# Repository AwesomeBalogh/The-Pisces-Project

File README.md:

The Pisces Project
By Bennett Balogh 
(Name subject to change Orion?)

This is a PCB with a 68 key layout like the ikki 68 aurora with left f keys using atmega chip.
The ultimate goal is to create a fully wireless pcb with wireless charging from a charger under the desk.

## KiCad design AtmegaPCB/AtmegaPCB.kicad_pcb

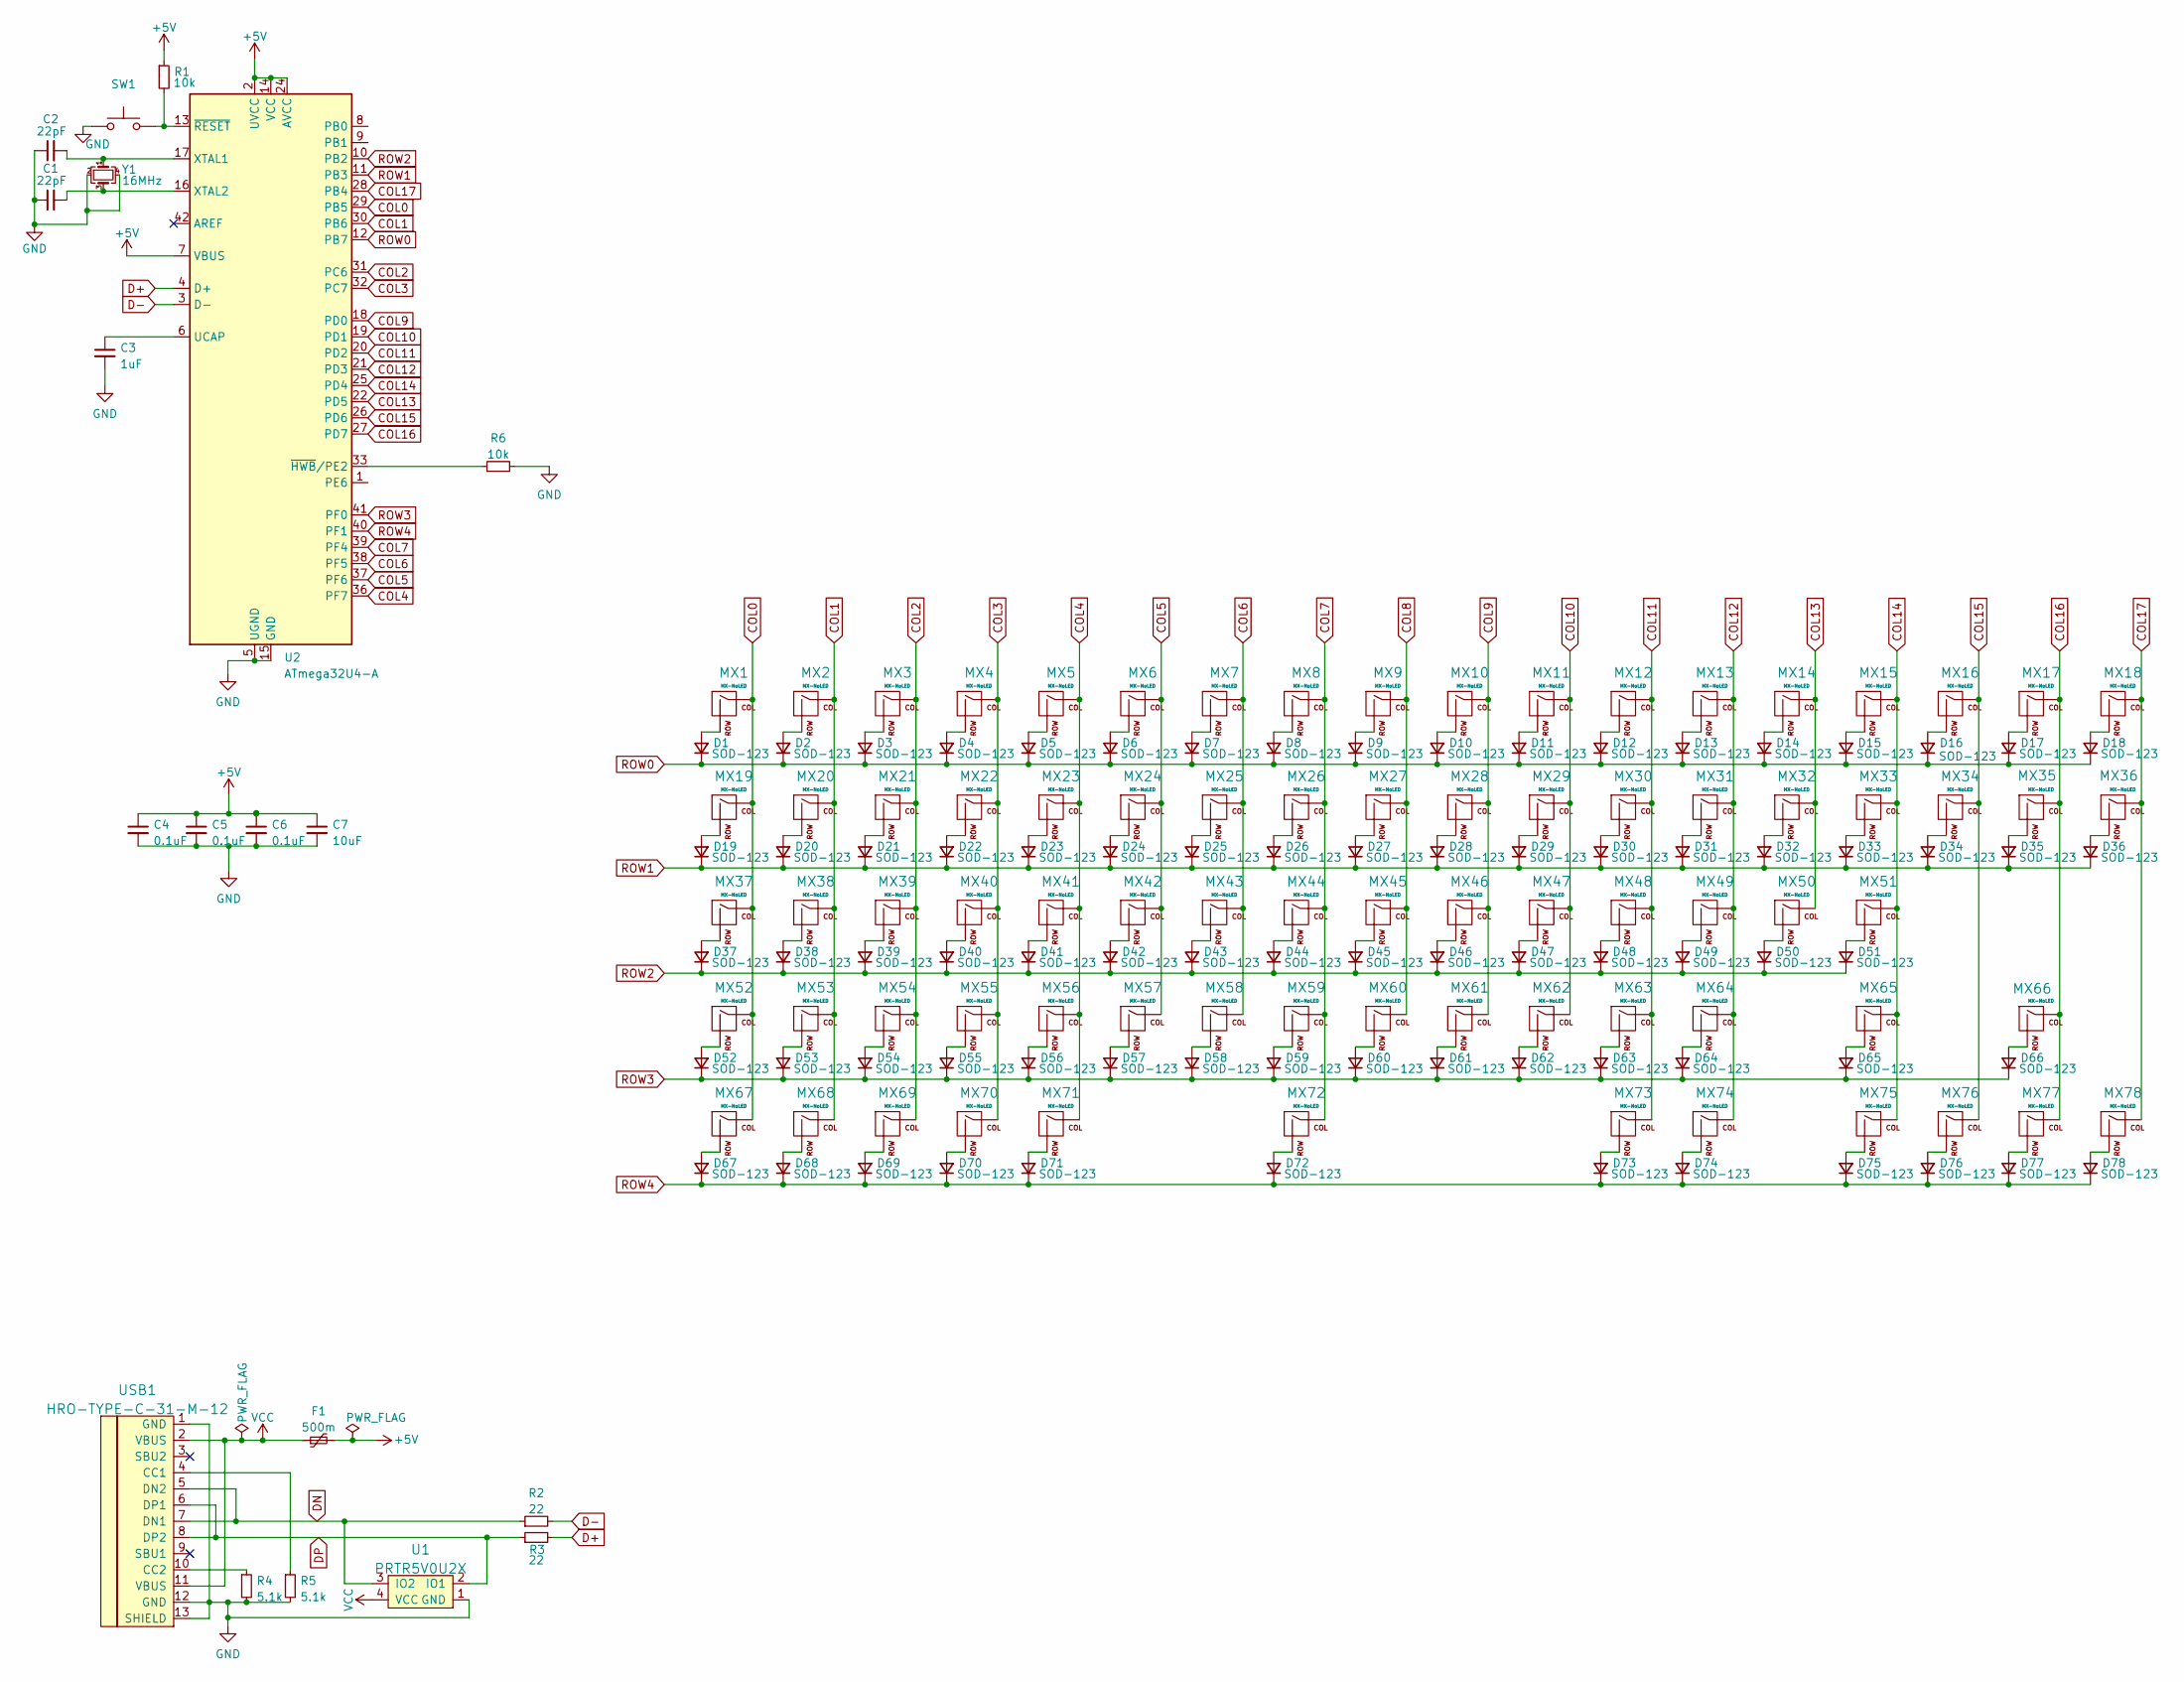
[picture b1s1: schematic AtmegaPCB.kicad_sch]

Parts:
C1, C2: 22pF; C_0805_2012Metric
C3: 1uF; C_0805_2012Metric
C4, C5, C6: 0.1uF; C_0805_2012Metric
C7: 10uF; C_0805_2012Metric
D1, D2, D3, D4, D5, D6, D7, D8, D9, D10, D11, D12, D13, D14, D15, D16, D17, D18, D19, D20, D21, D22, D23, D24, D25, D26, D27, D28, D29, D30, D31, D32, D33, D34, D35, D36, D37, D38, D39, D40, D41, D42, D43, D44, D45, D46, D47, D48, D49, D50, D51, D52, D53, D54, D55, D56, D57, D58, D59, D60, D61, D62, D63, D64, D65, D66, D67, D68, D69, D70, D71, D72, D73, D74, D75, D76, D77, D78: SOD-123; D_SOD-123
F1: 500m; Fuse_1206_3216Metric
MX1, MX2, MX3, MX4, MX5, MX6, MX7, MX8, MX9, MX10, MX11, MX12, MX13, MX14, MX15, MX17, MX18, MX19, MX20, MX22, MX23, MX24, MX25, MX26, MX27, MX28, MX29, MX30, MX31, MX32, MX33, MX35, MX36, MX37, MX38, MX40, MX41, MX42, MX43, MX44, MX45, MX46, MX47, MX48, MX49, MX50, MX52, MX53, MX55, MX56, MX57, MX58, MX59, MX60, MX61, MX62, MX63, MX64, MX66, MX67, MX68, MX76, MX77, MX78: MX-NoLED; MX-1U-NoLED
MX16: MX-NoLED; MX-2U-NoLED
MX21, MX34: MX-NoLED; MX-1.5U-NoLED
MX39: MX-NoLED; MX-1.75U-NoLED
MX51, MX54: MX-NoLED; MX-2.25U-NoLED
MX65: MX-NoLED; MX-2.75U-NoLED
MX69, MX70, MX71, MX73, MX74, MX75: MX-NoLED; MX-1.25U-NoLED
MX72: MX-NoLED; MX-6.25U-ReversedStabilizers-NoLED
R1, R6: 10k; R_0805_2012Metric
R2, R3: 22; R_0805_2012Metric
R4, R5: 5.1k; R_0805_2012Metric
SW1: (no value)
U1: PRTR5V0U2X; SOT143B
U2: ATmega32U4-A; TQFP-44_10x10mm_P0.8mm
USB1: HRO-TYPE-C-31-M-12; HRO-TYPE-C-31-M-12-Assembly
Y1: 16MHz; Crystal_SMD_3225-4Pin_3.2x2.5mm

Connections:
+5V: C4.1, C5.1, C6.1, C7.1, F1.2, R1.1, U2.2 (UVCC), U2.7 (VBUS), U2.14 (VCC), U2.24 (AVCC), U2.34 (VCC), U2.44 (AVCC)
COL0: MX1.1 (COL), MX19.1 (COL), MX37.1 (COL), MX52.1 (COL), MX67.1 (COL), U2.29 (PB5)
COL1: MX2.1 (COL), MX20.1 (COL), MX38.1 (COL), MX53.1 (COL), MX68.1 (COL), U2.30 (PB6)
COL2: MX3.1 (COL), MX21.1 (COL), MX39.1 (COL), MX54.1 (COL), MX69.1 (COL), U2.31 (PC6)
COL3: MX4.1 (COL), MX22.1 (COL), MX40.1 (COL), MX55.1 (COL), MX70.1 (COL), U2.32 (PC7)
COL4: MX5.1 (COL), MX23.1 (COL), MX41.1 (COL), MX56.1 (COL), MX71.1 (COL), U2.36 (PF7)
COL5: MX6.1 (COL), MX24.1 (COL), MX42.1 (COL), MX57.1 (COL), U2.37 (PF6)
COL6: MX7.1 (COL), MX25.1 (COL), MX43.1 (COL), MX58.1 (COL), U2.38 (PF5)
COL7: MX8.1 (COL), MX26.1 (COL), MX44.1 (COL), MX59.1 (COL), MX72.1 (COL), U2.39 (PF4)
COL8: MX9.1 (COL), MX27.1 (COL), MX45.1 (COL), MX60.1 (COL)
COL9: MX10.1 (COL), MX28.1 (COL), MX46.1 (COL), MX61.1 (COL), U2.18 (PD0)
COL10: MX11.1 (COL), MX29.1 (COL), MX47.1 (COL), MX62.1 (COL), U2.19 (PD1)
COL11: MX12.1 (COL), MX30.1 (COL), MX48.1 (COL), MX63.1 (COL), MX73.1 (COL), U2.20 (PD2)
COL12: MX13.1 (COL), MX31.1 (COL), MX49.1 (COL), MX64.1 (COL), MX74.1 (COL), U2.21 (PD3)
COL13: MX14.1 (COL), MX32.1 (COL), MX50.1 (COL), U2.22 (PD5)
COL14: MX15.1 (COL), MX33.1 (COL), MX51.1 (COL), MX65.1 (COL), MX75.1 (COL), U2.25 (PD4)
COL15: MX16.1 (COL), MX34.1 (COL), MX76.1 (COL), U2.26 (PD6)
COL16: MX17.1 (COL), MX35.1 (COL), MX66.1 (COL), MX77.1 (COL), U2.27 (PD7)
COL17: MX18.1 (COL), MX36.1 (COL), MX78.1 (COL), U2.28 (PB4)
D+: R3.2, U2.4 (D+)
D-: R2.2, U2.3 (D-)
DN: R2.1, U1.3 (IO2), USB1.5 (DN2), USB1.7 (DN1)
DP: R3.1, U1.2 (IO1), USB1.6 (DP1), USB1.8 (DP2)
GND: C1.1, C2.1, C3.2, C4.2, C5.2, C6.2, C7.2, R4.2, R5.2, R6.2, SW1.1, U1.1 (GND), U2.5 (UGND), U2.15 (GND), U2.23 (GND), U2.35 (GND), U2.43 (GND), USB1.1 (GND), USB1.12 (GND), USB1.13 (SHIELD), Y1.2, Y1.4
unnamed: C1.2, U2.16 (XTAL2), Y1.3
unnamed: C2.2, U2.17 (XTAL1), Y1.1
unnamed: C3.1, U2.6 (UCAP)
unnamed: D1.2 (A), MX1.2 (ROW)
unnamed: D2.2 (A), MX2.2 (ROW)
unnamed: D3.2 (A), MX3.2 (ROW)
unnamed: D4.2 (A), MX4.2 (ROW)
unnamed: D5.2 (A), MX5.2 (ROW)
unnamed: D6.2 (A), MX6.2 (ROW)
unnamed: D7.2 (A), MX7.2 (ROW)
unnamed: D8.2 (A), MX8.2 (ROW)
unnamed: D9.2 (A), MX9.2 (ROW)
unnamed: D10.2 (A), MX10.2 (ROW)
unnamed: D11.2 (A), MX11.2 (ROW)
unnamed: D12.2 (A), MX12.2 (ROW)
unnamed: D13.2 (A), MX13.2 (ROW)
unnamed: D14.2 (A), MX14.2 (ROW)
unnamed: D15.2 (A), MX15.2 (ROW)
unnamed: D16.2 (A), MX16.2 (ROW)
unnamed: D17.2 (A), MX17.2 (ROW)
unnamed: D18.2 (A), MX18.2 (ROW)
unnamed: D19.2 (A), MX19.2 (ROW)
unnamed: D20.2 (A), MX20.2 (ROW)
unnamed: D21.2 (A), MX21.2 (ROW)
unnamed: D22.2 (A), MX22.2 (ROW)
unnamed: D23.2 (A), MX23.2 (ROW)
unnamed: D24.2 (A), MX24.2 (ROW)
unnamed: D25.2 (A), MX25.2 (ROW)
unnamed: D26.2 (A), MX26.2 (ROW)
unnamed: D27.2 (A), MX27.2 (ROW)
unnamed: D28.2 (A), MX28.2 (ROW)
unnamed: D29.2 (A), MX29.2 (ROW)
unnamed: D30.2 (A), MX30.2 (ROW)
unnamed: D31.2 (A), MX31.2 (ROW)
unnamed: D32.2 (A), MX32.2 (ROW)
unnamed: D33.2 (A), MX33.2 (ROW)
unnamed: D34.2 (A), MX34.2 (ROW)
unnamed: D35.2 (A), MX35.2 (ROW)
unnamed: D36.2 (A), MX36.2 (ROW)
unnamed: D37.2 (A), MX37.2 (ROW)
unnamed: D38.2 (A), MX38.2 (ROW)
unnamed: D39.2 (A), MX39.2 (ROW)
unnamed: D40.2 (A), MX40.2 (ROW)
unnamed: D41.2 (A), MX41.2 (ROW)
unnamed: D42.2 (A), MX42.2 (ROW)
unnamed: D43.2 (A), MX43.2 (ROW)
unnamed: D44.2 (A), MX44.2 (ROW)
unnamed: D45.2 (A), MX45.2 (ROW)
unnamed: D46.2 (A), MX46.2 (ROW)
unnamed: D47.2 (A), MX47.2 (ROW)
unnamed: D48.2 (A), MX48.2 (ROW)
unnamed: D49.2 (A), MX49.2 (ROW)
unnamed: D50.2 (A), MX50.2 (ROW)
unnamed: D51.2 (A), MX51.2 (ROW)
unnamed: D52.2 (A), MX52.2 (ROW)
unnamed: D53.2 (A), MX53.2 (ROW)
unnamed: D54.2 (A), MX54.2 (ROW)
unnamed: D55.2 (A), MX55.2 (ROW)
unnamed: D56.2 (A), MX56.2 (ROW)
unnamed: D57.2 (A), MX57.2 (ROW)
unnamed: D58.2 (A), MX58.2 (ROW)
unnamed: D59.2 (A), MX59.2 (ROW)
unnamed: D60.2 (A), MX60.2 (ROW)
unnamed: D61.2 (A), MX61.2 (ROW)
unnamed: D62.2 (A), MX62.2 (ROW)
unnamed: D63.2 (A), MX63.2 (ROW)
unnamed: D64.2 (A), MX64.2 (ROW)
unnamed: D65.2 (A), MX65.2 (ROW)
unnamed: D66.2 (A), MX66.2 (ROW)
unnamed: D67.2 (A), MX67.2 (ROW)
unnamed: D68.2 (A), MX68.2 (ROW)
unnamed: D69.2 (A), MX69.2 (ROW)
unnamed: D70.2 (A), MX70.2 (ROW)
unnamed: D71.2 (A), MX71.2 (ROW)
unnamed: D72.2 (A), MX72.2 (ROW)
unnamed: D73.2 (A), MX73.2 (ROW)
unnamed: D74.2 (A), MX74.2 (ROW)
unnamed: D75.2 (A), MX75.2 (ROW)
unnamed: D76.2 (A), MX76.2 (ROW)
unnamed: D77.2 (A), MX77.2 (ROW)
unnamed: D78.2 (A), MX78.2 (ROW)
unnamed: R1.2, SW1.2, U2.13 (~RESET)
unnamed: R4.1, USB1.10 (CC2)
unnamed: R5.1, USB1.4 (CC1)
unnamed: R6.1, U2.33 (~HWB/PE2)
ROW0: D1.1 (K), D2.1 (K), D3.1 (K), D4.1 (K), D5.1 (K), D6.1 (K), D7.1 (K), D8.1 (K), D9.1 (K), D10.1 (K), D11.1 (K), D12.1 (K), D13.1 (K), D14.1 (K), D15.1 (K), D16.1 (K), D17.1 (K), D18.1 (K), U2.12 (PB7)
ROW1: D19.1 (K), D20.1 (K), D21.1 (K), D22.1 (K), D23.1 (K), D24.1 (K), D25.1 (K), D26.1 (K), D27.1 (K), D28.1 (K), D29.1 (K), D30.1 (K), D31.1 (K), D32.1 (K), D33.1 (K), D34.1 (K), D35.1 (K), D36.1 (K), U2.11 (PB3)
ROW2: D37.1 (K), D38.1 (K), D39.1 (K), D40.1 (K), D41.1 (K), D42.1 (K), D43.1 (K), D44.1 (K), D45.1 (K), D46.1 (K), D47.1 (K), D48.1 (K), D49.1 (K), D50.1 (K), D51.1 (K), U2.10 (PB2)
ROW3: D52.1 (K), D53.1 (K), D54.1 (K), D55.1 (K), D56.1 (K), D57.1 (K), D58.1 (K), D59.1 (K), D60.1 (K), D61.1 (K), D62.1 (K), D63.1 (K), D64.1 (K), D65.1 (K), D66.1 (K), U2.41 (PF0)
ROW4: D67.1 (K), D68.1 (K), D69.1 (K), D70.1 (K), D71.1 (K), D72.1 (K), D73.1 (K), D74.1 (K), D75.1 (K), D76.1 (K), D77.1 (K), D78.1 (K), U2.40 (PF1)
VCC: F1.1, U1.4 (VCC), USB1.2 (VBUS), USB1.11 (VBUS)

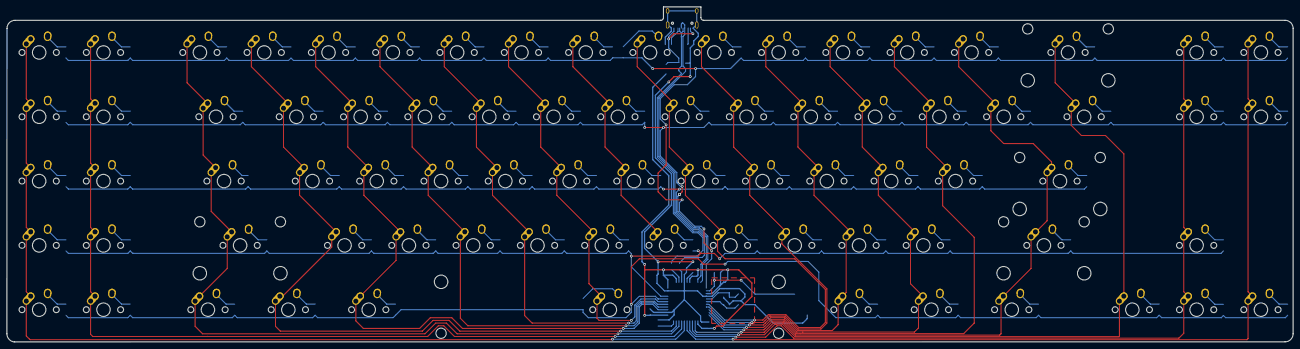
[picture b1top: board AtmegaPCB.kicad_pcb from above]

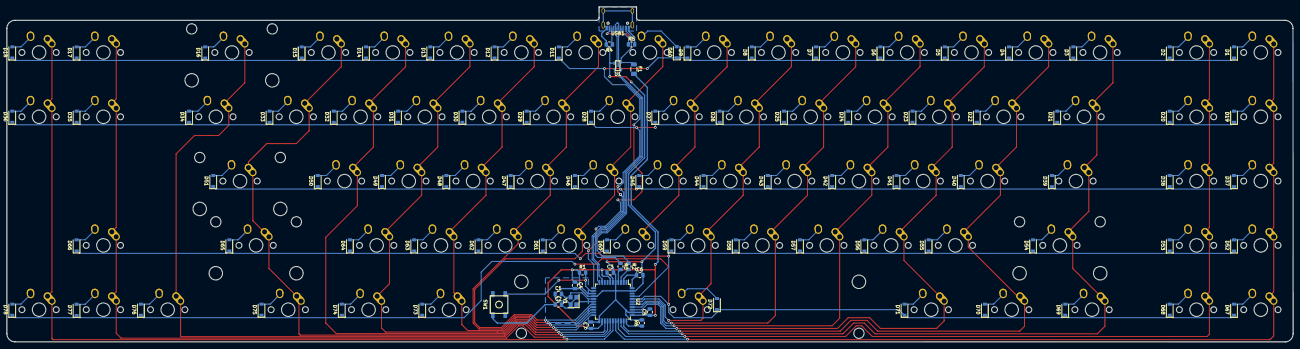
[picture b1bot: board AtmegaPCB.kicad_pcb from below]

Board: 2 copper layers, 381.0 x 99.2 mm, 175 parts (97 on the bottom side), 115 nets.

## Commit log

2022-04-23 Inicialized Project
2022-04-23 Added Lib Tables
2022-04-23 MCU Done
2022-04-23 USB Start
2022-04-24 USB Circit Built
2022-04-24 Matrix done!
2022-04-24 Added footprints
2022-04-25 Added missed keys
2022-04-25 Matrix Start
2022-04-25 Keymap Setup
2022-04-25 Matrix Update2
2022-04-25 Routed Vertical Traces
2022-04-25 Traces Started
2022-04-26 COL & ROW Traced
2022-04-26 Traces Completed
2022-04-26 For Review
2022-04-26 bolded
2022-04-26 Edited
